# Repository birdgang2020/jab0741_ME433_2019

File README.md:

# jab0741_ME433_2019

#Jacob Beran 4/3/2019
#Code for ME433

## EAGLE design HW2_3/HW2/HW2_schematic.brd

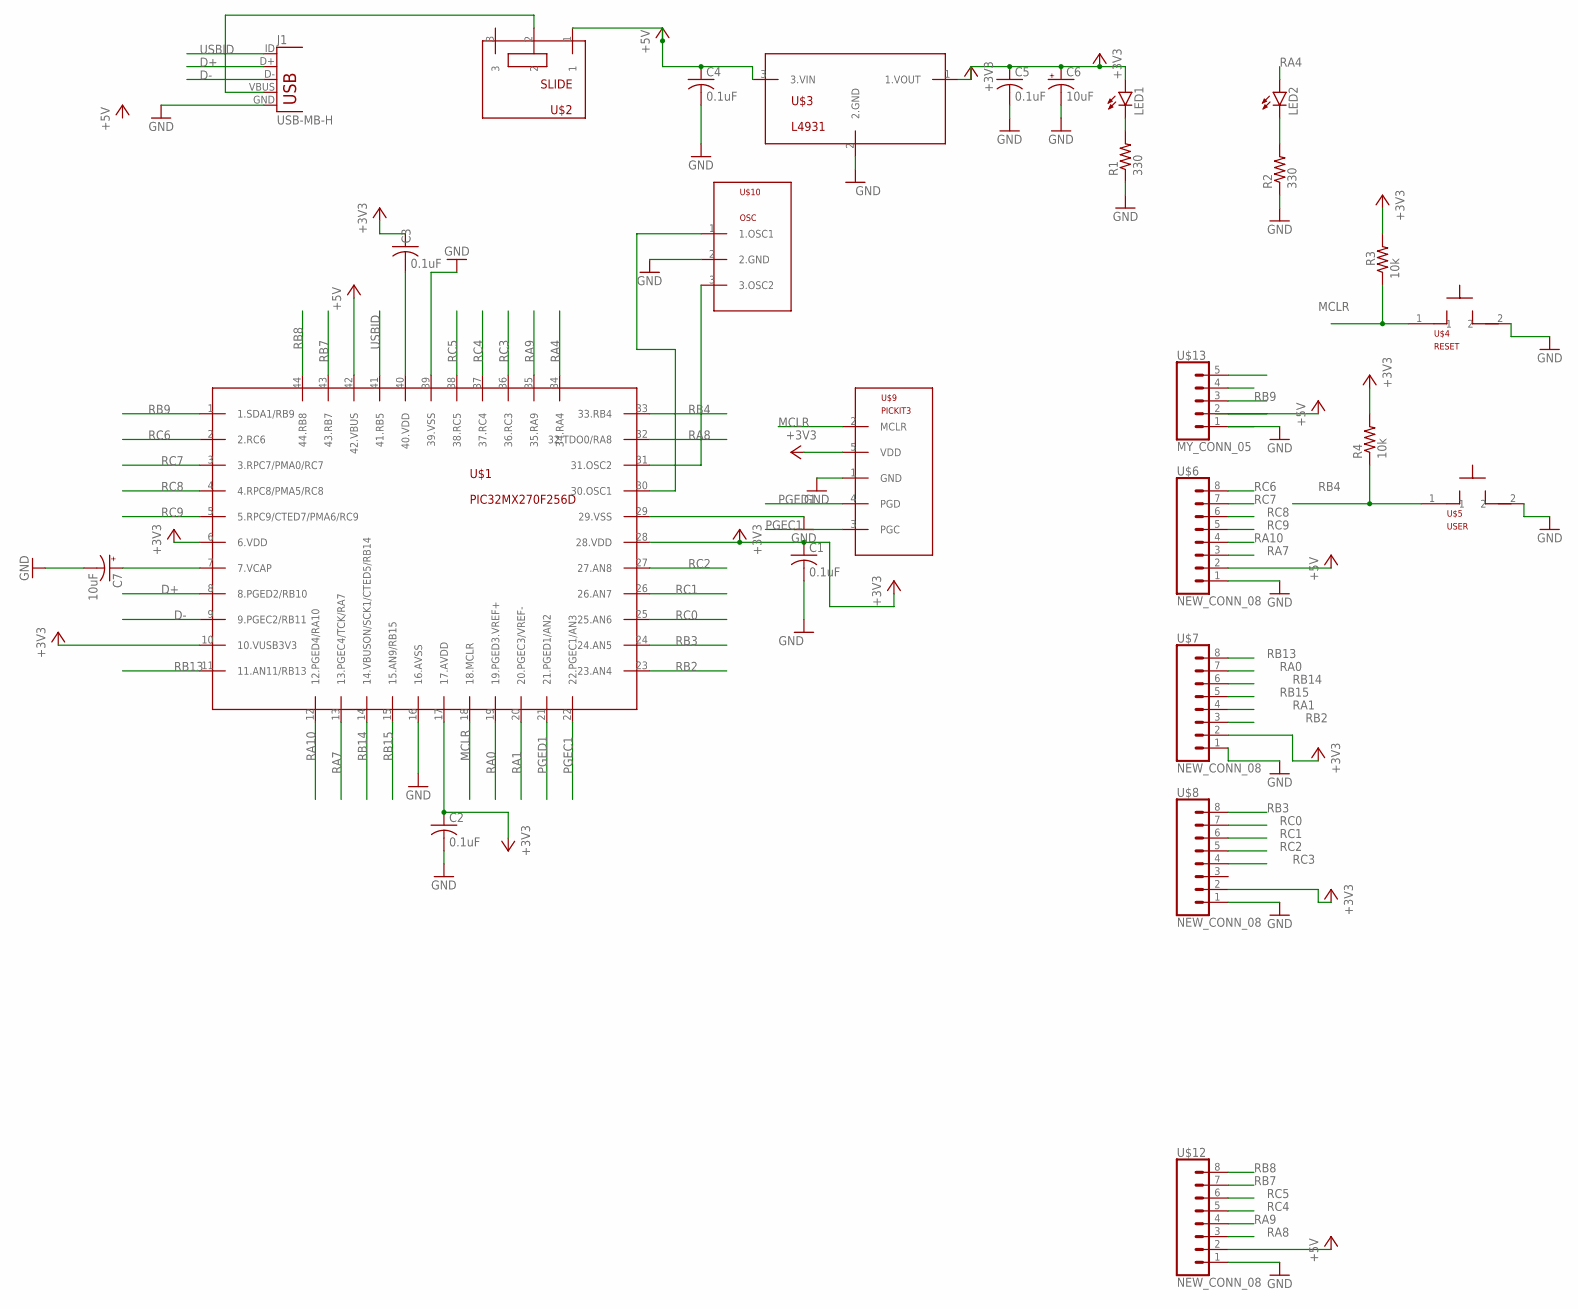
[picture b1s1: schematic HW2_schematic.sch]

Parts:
C1, C2, C3, C4, C5: 0.1uF; C025-025X050
C6, C7: 10uF; B45181B
J1: USB-MB-H
LED1, LED2: LED3MM
R1, R2: 330; 0207/10
R3, R4: 10k; 0207/10
U$1: PIC32MX270F256D; QFN44ML8X8
U$2: SLIDE
U$3: L4931; TO92
U$4: RESET; PB
U$5: USER; PB
U$6, U$7, U$8, U$12: NEW_CONN_08; 1X08
U$9: PICKIT3; 1X05
U$10: OSC
U$13: MY_CONN_05; 1X05

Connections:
+3V3: C1.1, C2.1, C3.1, C5.1, C6.+, LED1.A, R3.2, R4.2, U$1.6 (6.VDD), U$1.10 (10.VUSB3V3), U$1.17 (17.AVDD), U$1.28 (28.VDD), U$3.1 (1.VOUT), U$7.2, U$8.2, U$9.5 (VDD)
+5V: C4.1, U$1.42 (42.VBUS), U$2.1, U$3.3 (3.VIN), U$6.2, U$12.2
D+: J1.D+, U$1.8 (8.PGED2/RB10)
D-: J1.D-, U$1.9 (9.PGEC2/RB11)
GND: C1.2, C2.2, C4.2, C5.2, C6.-, C7.-, J1.GND, R1.1, R2.1, U$1.16 (16.AVSS), U$1.29 (29.VSS), U$1.39 (39.VSS), U$3.2 (2.GND), U$4.2, U$5.2, U$6.1, U$7.1, U$8.1, U$9.1 (GND), U$10.2 (2.GND), U$12.1
MCLR: R3.1, U$1.18 (18.MCLR), U$4.1, U$9.2 (MCLR)
unnamed: J1.VBUS, U$2.2
unnamed: LED1.K (C), R1.2
unnamed: LED2.K (C), R2.2
unnamed: U$1.30 (30.OSC1), U$10.1 (1.OSC1)
unnamed: U$1.31 (31.OSC2), U$10.3 (3.OSC2)
unnamed: C3.2, U$1.40 (40.VDD)
unnamed: C7.+, U$1.7 (7.VCAP)
PGEC1: U$1.22 (22.PGEC1/AN3), U$9.3 (PGC)
PGED1: U$1.21 (21.PGED1/AN2), U$9.4 (PGD)
RA0: U$1.19 (19.PGED3.VREF+), U$7.7
RA1: U$1.20 (20.PGEC3/VREF-), U$7.4
RA4: LED2.A, U$1.34 (34.RA4)
RA7: U$1.13 (13.PGEC4/TCK/RA7), U$6.3
RA8: U$1.32 (32.TDO0/RA8), U$12.3
RA9: U$1.35 (35.RA9), U$12.4
RA10: U$1.12 (12.PGED4/RA10), U$6.4
RB2: U$1.23 (23.AN4), U$7.3
RB3: U$1.24 (24.AN5), U$8.8
RB4: R4.1, U$1.33 (33.RB4), U$5.1
RB7: U$1.43 (43.RB7), U$12.7
RB8: U$1.44 (44.RB8), U$12.8
RB9: U$1.1 (1.SDA1/RB9), U$13.3
RB13: U$1.11 (11.AN11/RB13), U$7.8
RB14: U$1.14 (14.VBUSON/SCK1/CTED5/RB14), U$7.6
RB15: U$1.15 (15.AN9/RB15), U$7.5
RC0: U$1.25 (25.AN6), U$8.7
RC1: U$1.26 (26.AN7), U$8.6
RC2: U$1.27 (27.AN8), U$8.5
RC3: U$1.36 (36.RC3), U$8.4
RC4: U$1.37 (37.RC4), U$12.5
RC5: U$1.38 (38.RC5), U$12.6
RC6: U$1.2 (2.RC6), U$6.8
RC7: U$1.3 (3.RPC7/PMA0/RC7), U$6.7
RC8: U$1.4 (4.RPC8/PMA5/RC8), U$6.6
RC9: U$1.5 (5.RPC9/CTED7/PMA6/RC9), U$6.5
USBID: J1.ID, U$1.41 (41.RB5)

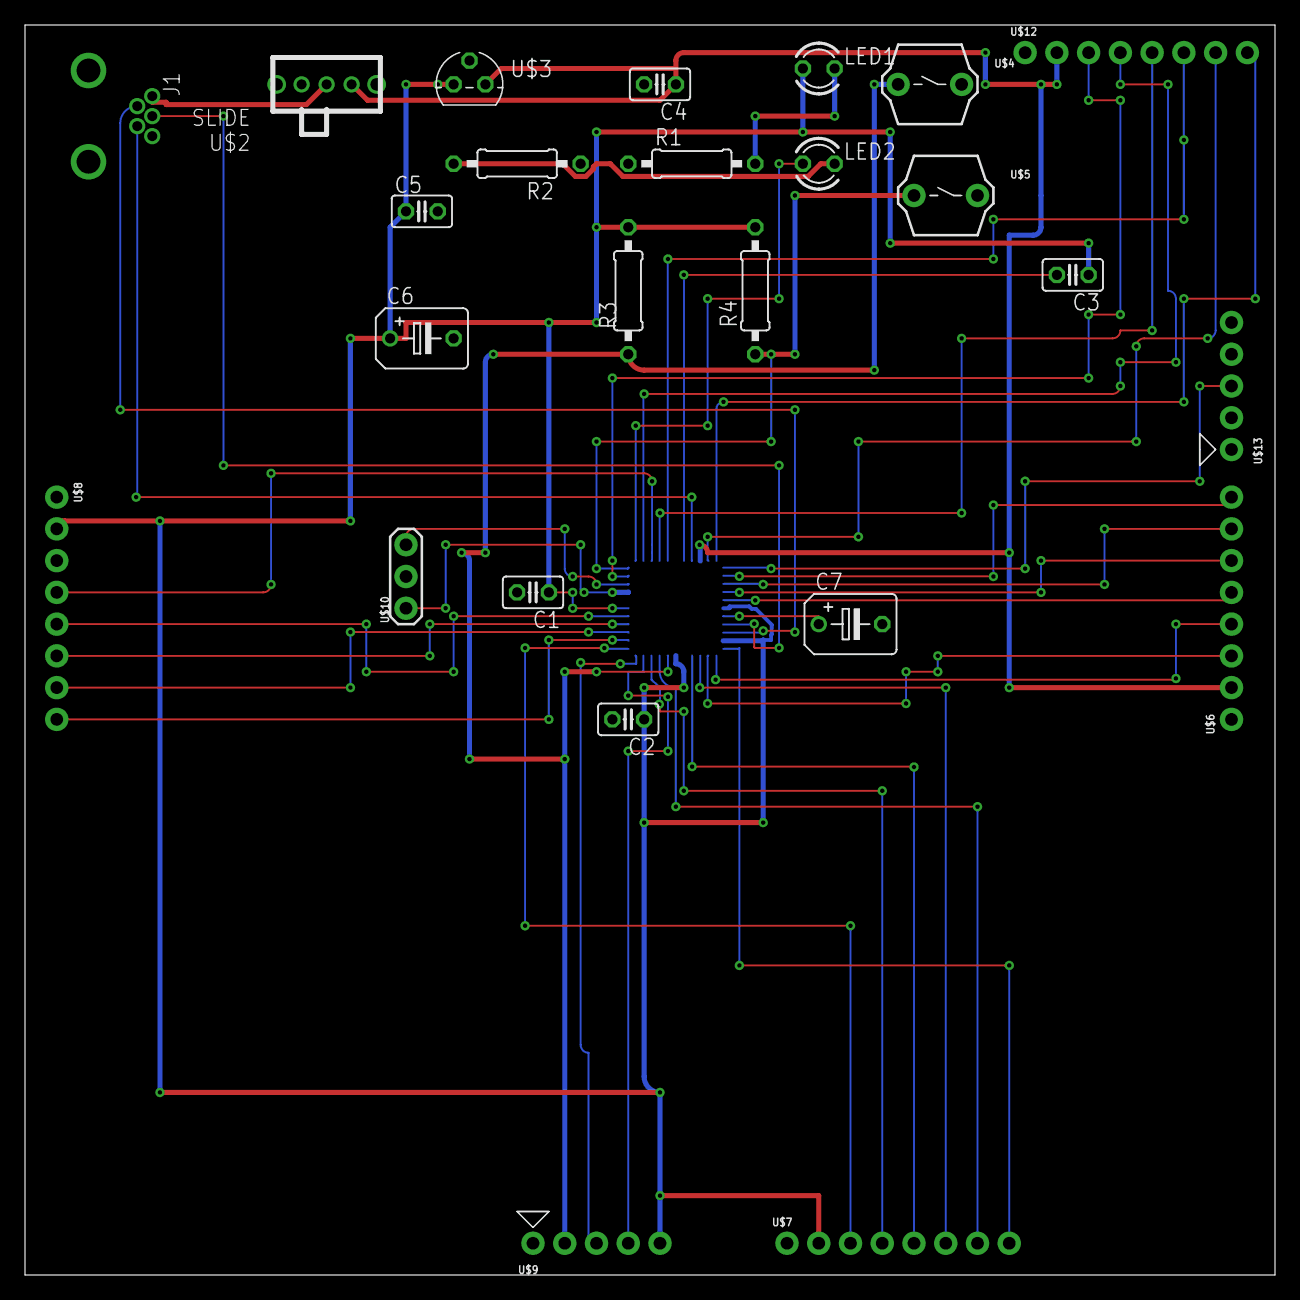
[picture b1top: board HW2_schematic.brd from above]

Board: 2 copper layers, 100.0 x 100.0 mm, 26 parts (1 on the bottom side), 42 nets.

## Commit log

2019-04-04 Create HW1.2_input_capacitor.png
    One input capacitor .1uF
2019-04-04 Create HW1.2_input_and_output_capacitor.png
    Two .1 uF capacitors on input and output
2019-04-04 Create HW1.2_input_and_output_capacitors.png
    Two output capacitors and one input capacitor
2019-04-04 Create IMG_1276.jpg
    Photo of Breadboard
2019-04-04 Create IMG_1278.jpg
    Circuit Diagram
2019-04-04 Create HW1.c
    Putting in sample code
2019-04-04 Update README.md
    Editing the readme
2019-04-04 Creating a new project for HW1
2019-04-04 Update HW1.c
    Adding in LEDs
2019-04-04 Getting the file to compile
2019-04-05 Trying to debug the pic
2019-04-09 Adding new eagle files to the repo
2019-04-11 Fixing the initializations to get them to work using keywords
2019-04-15 adding in code to get led to toggle
2019-04-16 i've been copying and pasting the schematic into this folder since my project folder is somewhere else and i don't want to mess things up by trying to move it into here.
2019-04-18 Updating pushbutton to stop LED for HW1
2019-04-25 Moving files into hw1 folder
2019-05-16 setting up SPI between PIC and DAC, making a header file for all of the initializations for the PIC
2019-05-20 double checking configuration bits to copy to hw4
2019-05-23 put in initializations for SPI and PIC in main.c
2019-05-24 calling set voltage in main
2019-05-28 Moving files and folders around
2019-05-28 pictures for DAC
2019-05-28 Adding starter code to hw5
2019-05-28 rearranging files and starting main code
2019-05-30 editing main and putting in header files
2019-05-30 setting baud rate
2019-05-30 FInalizing code for HW5
2019-06-02 finishing hw6
2019-06-03 trying to debug the lcd screen
    LCD_init() is causing the program to stop because of an infinite loop, can't find errors in the circuitry
2019-06-03 wheel made
2019-06-04 Adding in gerber files and board files into repo
2019-06-05 adding hole to wheel
2019-06-05 side and bottom plate for box
2019-06-06 updating wheels and box
2019-06-06 debugging hw6
2019-06-08 hw6 working properly
2019-06-08 updating main
2019-06-08 using hw6 as template for hw7
2019-06-09 adding in I2C code
2019-06-09 working on hw7
2019-06-09 putting in boxes for hw7
2019-06-09 finishing touches
2019-06-10 Doing HW8
2019-06-11 making hw9 and updating wheels after first print for final robot
2019-06-12 Making new box CAD files and doing HW9
2019-06-12 v2 of solidworks box
    v1 living hinge did not work
2019-06-13 Finishing up the box(hopefully)
2019-06-13 organizing
2019-06-13 Box pictures
2019-06-14 Finishing HW9 and doing HW10
2019-06-15 hw15
2019-06-15 putting in chasis cad
2019-06-15 debugging hw15
